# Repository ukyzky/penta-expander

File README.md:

# penta-expander

## ryo penta sequencer expander (eurorack 4HP)

Currently manufacturing no problem. It works fine.

## function

- per step **trigger** output
- per step on/off switch
- summed **trigger** output
- hold on/off switch
- hold input (signal high: hold on)

## notes

pcb v1 is main function.

pcb v1plus is sub function of gate to trigger converter x5.

If using pcb v1 only, it becomes per step gate output and summed gate output.
In summed gate output, it has a problem that a step produces 2 triggers because the step fall down signal overwraps the next step's clock.

If using pcb v1 and v1plus, it becomes per step trigger output and summed trigger output.
Above gate problem is resolved.

## bom

refer kicad files.

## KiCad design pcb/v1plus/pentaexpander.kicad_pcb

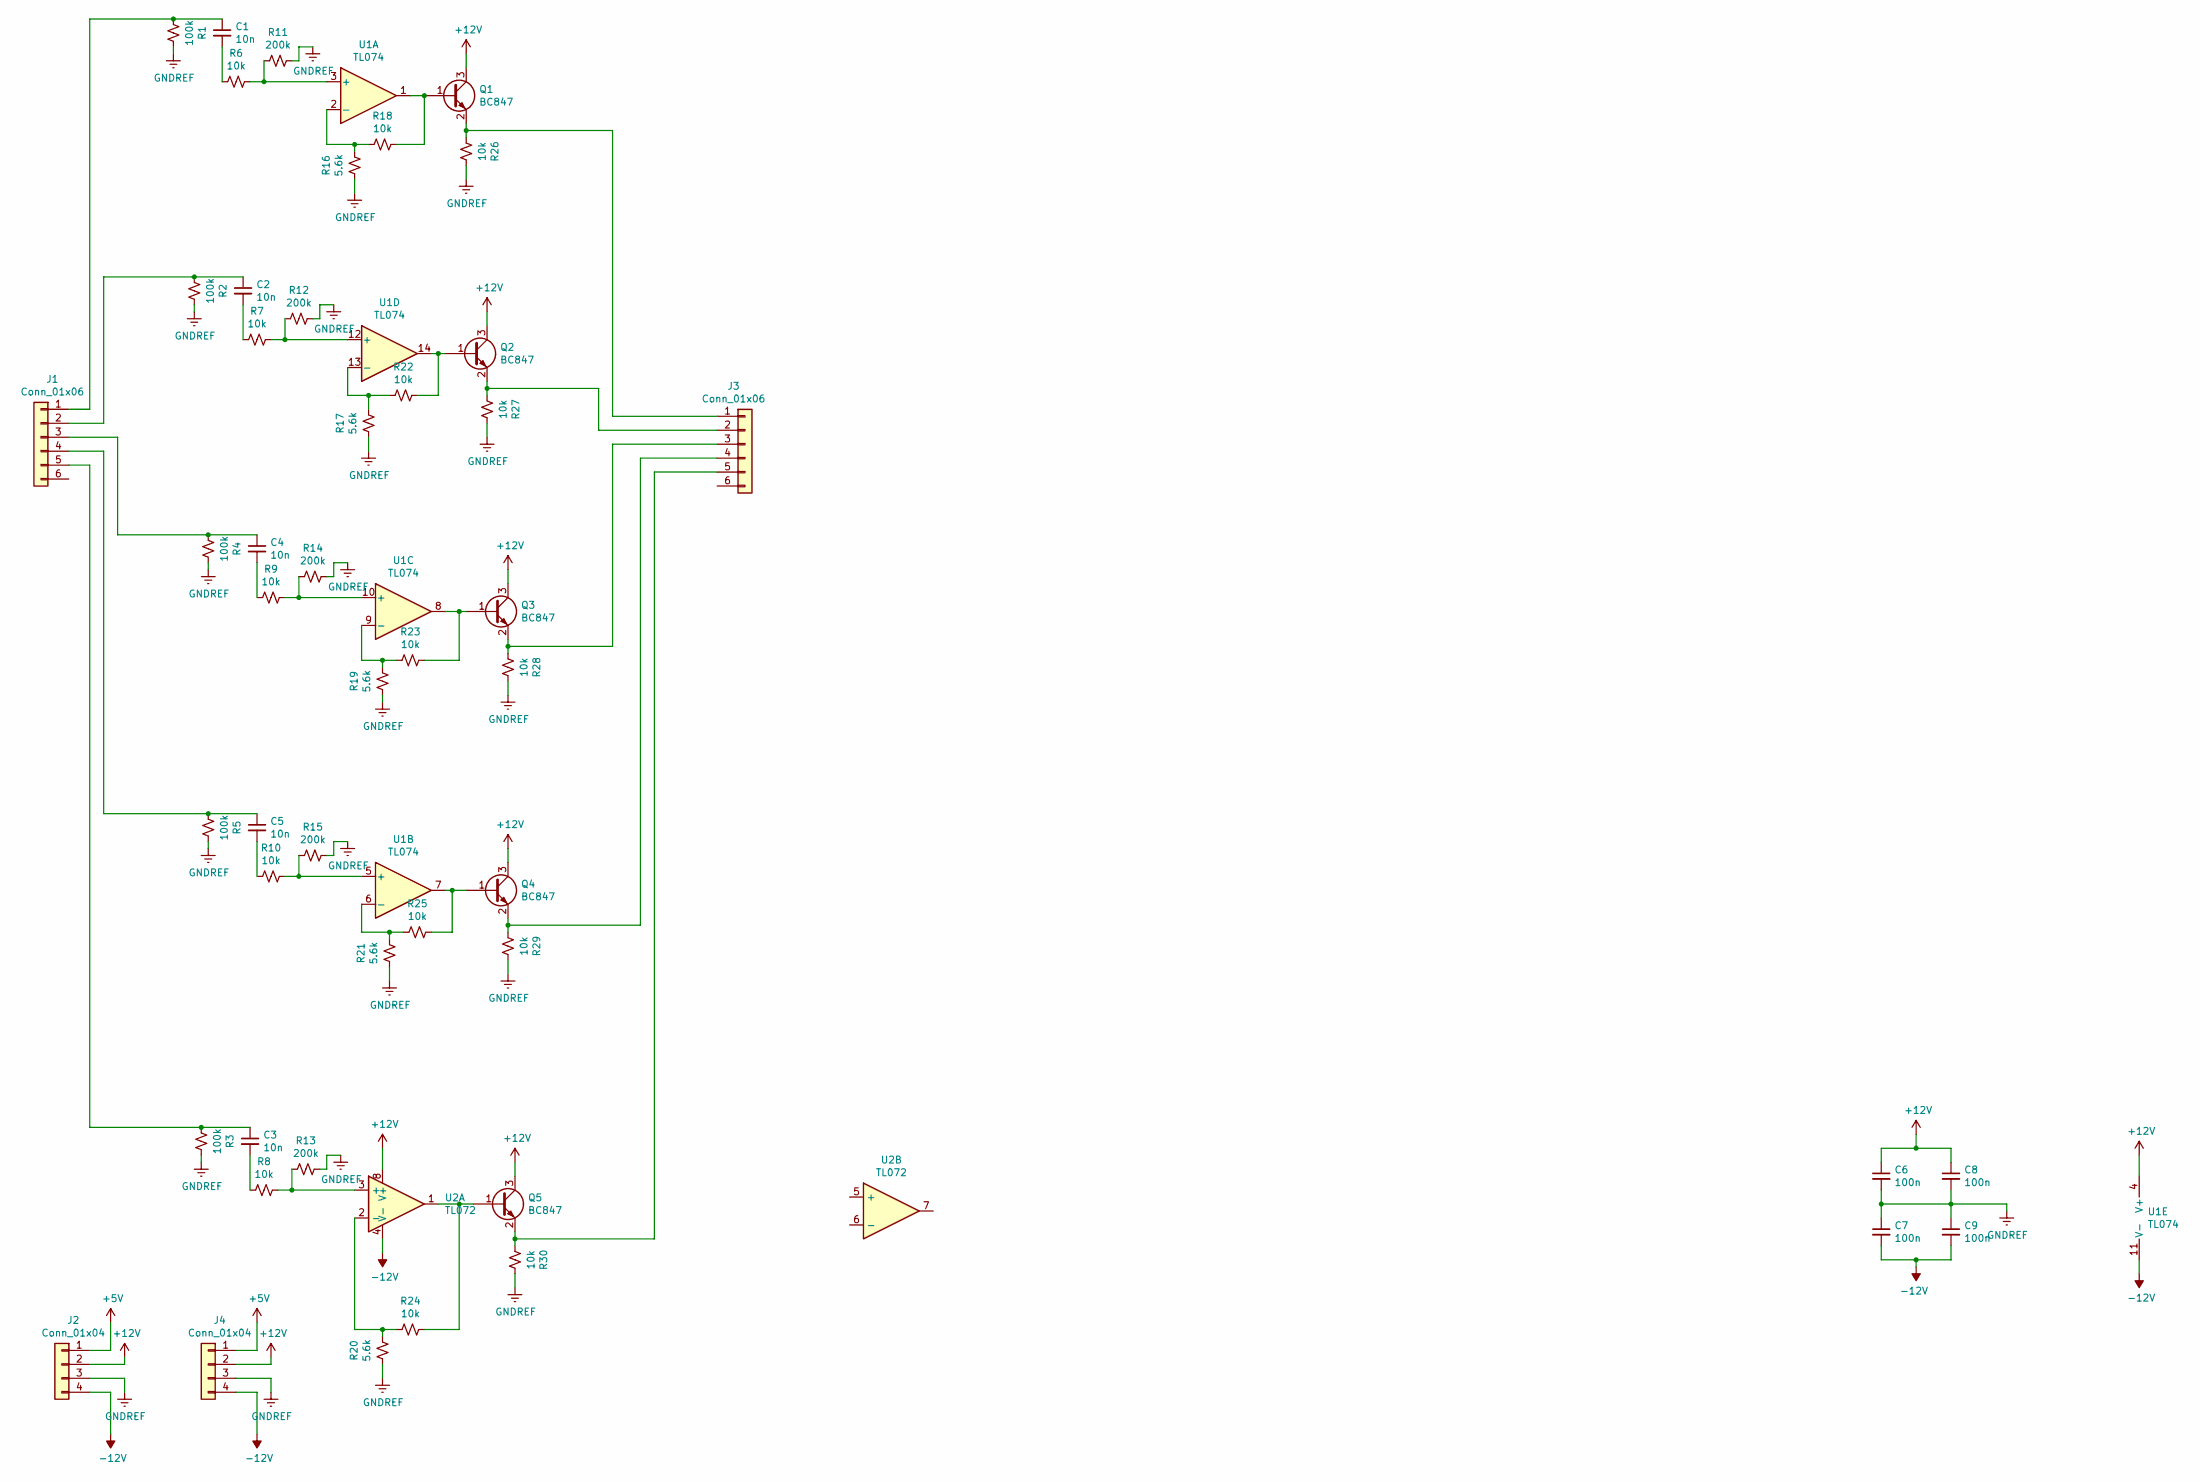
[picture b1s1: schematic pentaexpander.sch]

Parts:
C1, C2, C3, C4, C5: 10n; D_0805_2012Metric_Pad1.15x1.40mm_HandSolder
C6, C7, C8, C9: 100n; D_0805_2012Metric_Pad1.15x1.40mm_HandSolder
J1, J3: Conn_01x06; Pins_1x06_2.54mm_TH_SWD
J2, J4: Conn_01x04; Pins_1x04_2.54mm_TH
Q1, Q2, Q3, Q4, Q5: BC847; SOT-23
R1, R2, R3, R4, R5: 100k; R_0603_1608Metric_Pad1.05x0.95mm_HandSolder
R6, R7, R8, R9, R10, R18, R22, R23, R24, R25, R26, R27, R28, R29, R30: 10k; R_0603_1608Metric_Pad1.05x0.95mm_HandSolder
R11, R12, R13, R14, R15: 200k; R_0603_1608Metric_Pad1.05x0.95mm_HandSolder
R16, R17, R19, R20, R21: 5.6k; R_0603_1608Metric_Pad1.05x0.95mm_HandSolder
U1: TL074; SOIC-14_3.9x8.7mm_P1.27mm
U2: TL072; SOIC-8_3.9x4.9mm_Pitch1.27mm

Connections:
+5V: J2.1, J4.1
+12V: C6.1, C8.1, J2.2, J4.2, Q1.3 (C), Q2.3 (C), Q3.3 (C), Q4.3 (C), Q5.3 (C), U1.4 (V+), U2.8 (V+)
-12V: C7.2, C9.2, J2.4, J4.4, U1.11 (V-), U2.4 (V-)
GNDREF: C6.2, C7.1, C8.2, C9.1, J2.3, J4.3, R1.1, R2.1, R3.1, R4.1, R5.1, R11.1, R12.1, R13.1, R14.1, R15.1, R16.2, R17.2, R19.2, R20.2, R21.2, R26.1, R27.1, R28.1, R29.1, R30.1
unnamed: C1.1, J1.1, R1.2
unnamed: C1.2, R6.2
unnamed: C2.1, J1.2, R2.2
unnamed: C2.2, R7.2
unnamed: C3.1, J1.5, R3.2
unnamed: C3.2, R8.2
unnamed: C4.1, J1.3, R4.2
unnamed: C4.2, R9.2
unnamed: C5.1, J1.4, R5.2
unnamed: C5.2, R10.2
unnamed: J3.1, Q1.2 (E), R26.2
unnamed: J3.2, Q2.2 (E), R27.2
unnamed: J3.3, Q3.2 (E), R28.2
unnamed: J3.4, Q4.2 (E), R29.2
unnamed: J3.5, Q5.2 (E), R30.2
unnamed: Q1.1 (B), R18.1, U1.1
unnamed: Q2.1 (B), R22.1, U1.14
unnamed: Q3.1 (B), R23.1, U1.8
unnamed: Q4.1 (B), R25.1, U1.7
unnamed: Q5.1 (B), R24.1, U2.1
unnamed: R10.1, R15.2, U1.5 (+)
unnamed: R6.1, R11.2, U1.3 (+)
unnamed: R7.1, R12.2, U1.12 (+)
unnamed: R8.1, R13.2, U2.3 (+)
unnamed: R9.1, R14.2, U1.10 (+)
unnamed: R16.1, R18.2, U1.2 (-)
unnamed: R17.1, R22.2, U1.13 (-)
unnamed: R19.1, R23.2, U1.9 (-)
unnamed: R20.1, R24.2, U2.2 (-)
unnamed: R21.1, R25.2, U1.6 (-)

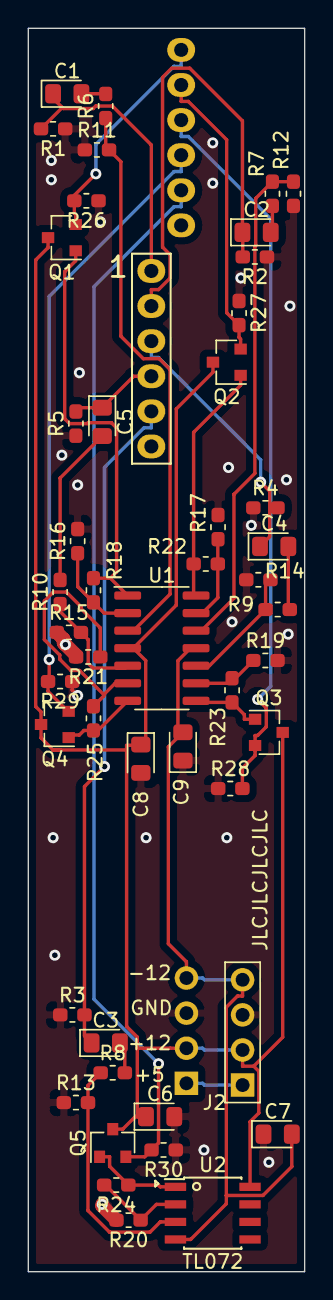
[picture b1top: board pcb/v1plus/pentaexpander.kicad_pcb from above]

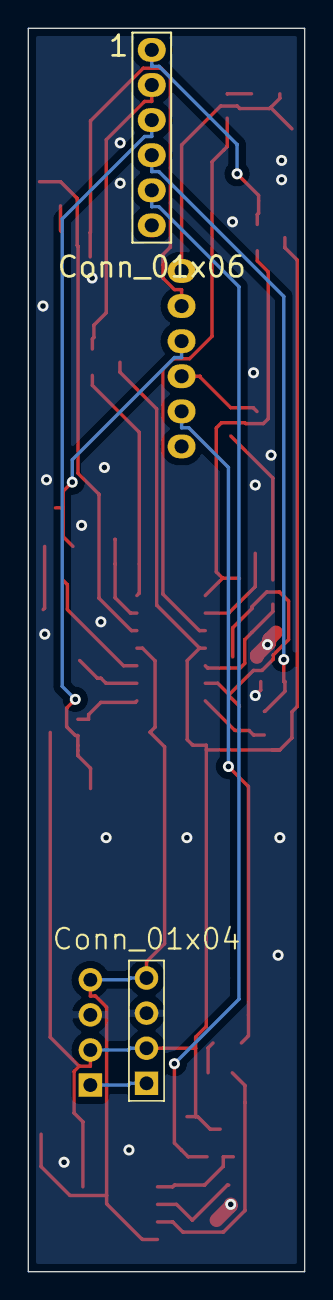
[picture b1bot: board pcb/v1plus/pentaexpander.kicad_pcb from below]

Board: 2 copper layers, 20.0 x 90.0 mm, 50 parts (2 on the bottom side), 34 nets.

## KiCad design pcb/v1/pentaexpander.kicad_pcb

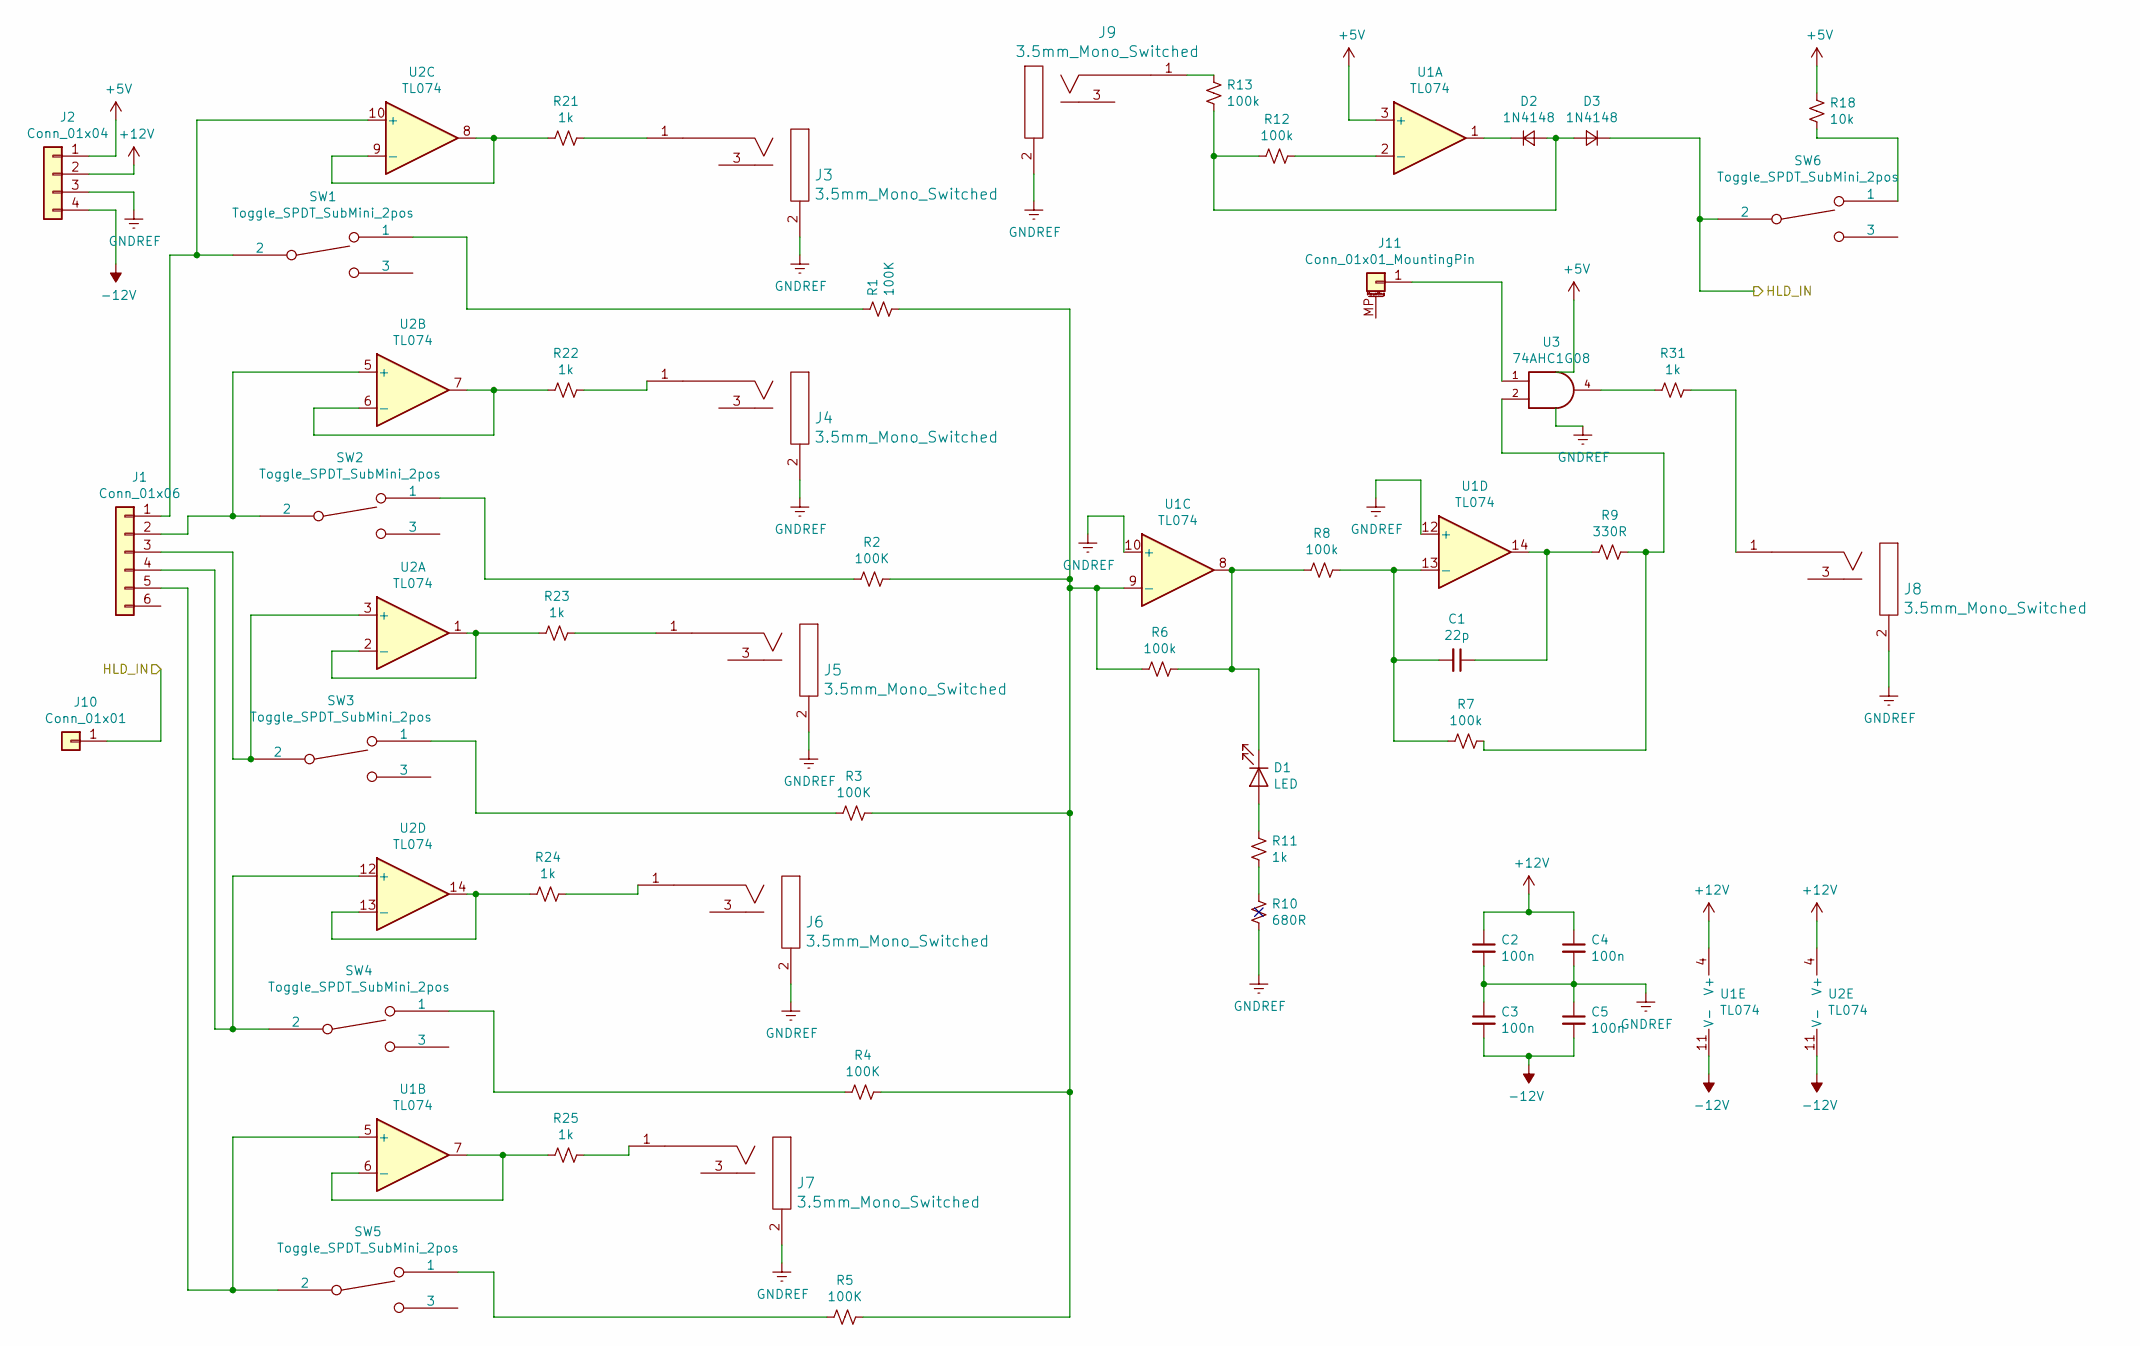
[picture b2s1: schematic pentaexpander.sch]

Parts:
C1: 22p; D_0805_2012Metric_Pad1.15x1.40mm_HandSolder
C2, C3, C4, C5: 100n; D_0805_2012Metric_Pad1.15x1.40mm_HandSolder
D1: LED; LED_D3.0mm
D2, D3: 1N4148; D_DO-15_P2.54mm_Vertical_AnodeUp
J1: Conn_01x06; Pins_1x06_2.54mm_TH_SWD
J2: Conn_01x04; Pins_1x04_2.54mm_TH
J3, J4, J5, J6, J7, J8, J9: 3.5mm_Mono_Switched; EighthInch_PJ398SM; Part Number WQP-WQP518MA
J10: Conn_01x01; PinHeader_1x01_P2.54mm_Vertical
J11: Conn_01x01_MountingPin; PinHeader_1x01_P2.54mm_Vertical
R1, R2, R3, R4, R5: 100K; R_0603_1608Metric_Pad1.05x0.95mm_HandSolder
R6, R7, R8, R12, R13: 100k; R_0603_1608Metric_Pad1.05x0.95mm_HandSolder
R9: 330R; R_0603_1608Metric_Pad1.05x0.95mm_HandSolder
R10: 680R; R_0603_1608Metric_Pad1.05x0.95mm_HandSolder
R11, R21, R22, R23, R24, R25, R31: 1k; R_0603_1608Metric_Pad1.05x0.95mm_HandSolder
R18: 10k; R_0603_1608Metric_Pad1.05x0.95mm_HandSolder
SW1, SW2, SW3, SW4, SW5, SW6: Toggle_SPDT_SubMini_2pos; Switch_Toggle_SPDT_SubMini; Part Number 200-MSP3-T2B3M2QE
U1, U2: TL074; SOIC-14_3.9x8.7mm_P1.27mm
U3: 74AHC1G08; SOT-23-5_HandSoldering

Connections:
+5V: J2.1, R18.1, U1.3 (+), U3.5 (VCC)
+12V: C2.1, C4.1, J2.2, U1.4 (V+), U2.4 (V+)
-12V: C3.2, C5.2, J2.4, U1.11 (V-), U2.11 (V-)
/HLD_IN: D3.1 (K), J10.1, SW6.2
GND: C2.2, C3.1, C4.2, C5.1, J2.3, J3.2 (SHEILD), J4.2 (SHEILD), J5.2 (SHEILD), J6.2 (SHEILD), J7.2 (SHEILD), J8.2 (SHEILD), J9.2 (SHEILD), R10.2, U1.10 (+), U1.12 (+), U3.3 (GND)
unnamed: C1.1, R9.2, U1.14
unnamed: C1.2, R7.2, R8.1, U1.13 (-)
unnamed: D1.1 (K), R6.1, R8.2, U1.8
unnamed: D1.2 (A), R11.1
unnamed: D2.1 (K), U1.1
unnamed: D2.2 (A), D3.2 (A), R12.2, R13.2
unnamed: J1.1, SW1.2, U2.10 (+)
unnamed: J1.2, SW2.2, U2.5 (+)
unnamed: J1.3, SW3.2, U2.3 (+)
unnamed: J1.4, SW4.2, U2.12 (+)
unnamed: J1.5, SW5.2, U1.5 (+)
unnamed: J3.1 (SIG), R21.1
unnamed: J4.1 (SIG), R22.1
unnamed: J5.1 (SIG), R23.1
unnamed: J6.1 (SIG), R24.1
unnamed: J7.1 (SIG), R25.1
unnamed: J8.1 (SIG), R31.1
unnamed: J9.1 (SIG), R13.1
unnamed 31: J11.1, U3.1; also elsewhere on the board
unnamed: R1.1, SW1.1
unnamed: R1.2, R2.1, R3.1, R4.1, R5.1, R6.2, U1.9 (-)
unnamed: R2.2, SW2.1
unnamed: R3.2, SW3.1
unnamed: R4.2, SW4.1
unnamed: R5.2, SW5.1
unnamed: R7.1, R9.1, U3.2
unnamed: R10.1, R11.2
unnamed: R12.1, U1.2 (-)
unnamed: R18.2, SW6.1
unnamed: R21.2, U2.8, U2.9 (-)
unnamed: R22.2, U2.6 (-), U2.7
unnamed: R23.2, U2.1, U2.2 (-)
unnamed: R24.2, U2.13 (-), U2.14
unnamed: R25.2, U1.6 (-), U1.7
unnamed: R31.2, U3.4

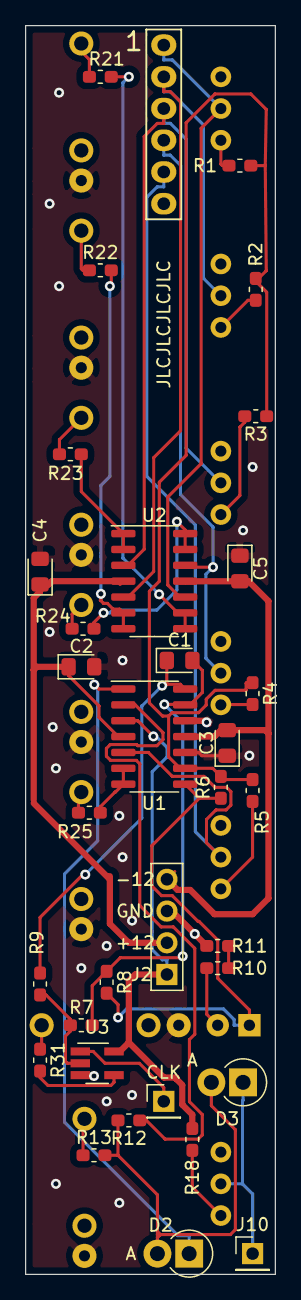
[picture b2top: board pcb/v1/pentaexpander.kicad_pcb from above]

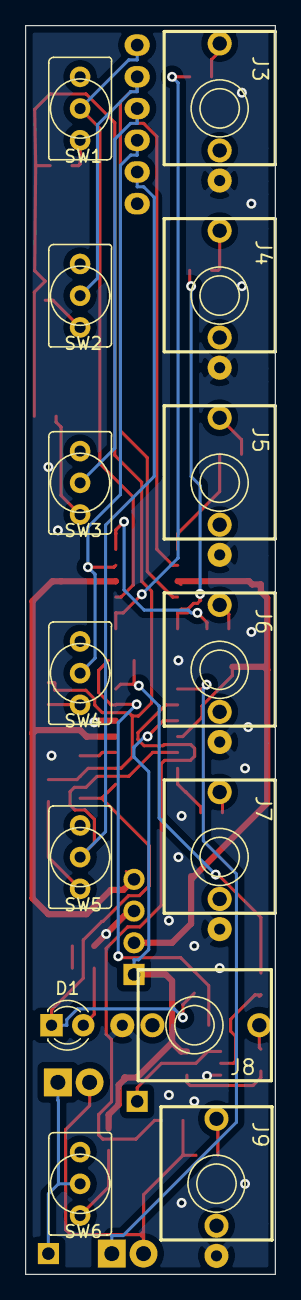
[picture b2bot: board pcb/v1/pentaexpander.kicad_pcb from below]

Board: 2 copper layers, 20.0 x 100.0 mm, 48 parts (14 on the bottom side), 40 nets.

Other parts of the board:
CLK: Conn_01x01_MountingPin; PinHeader_1x01_P2.54mm_Vertical

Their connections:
unnamed 31: CLK.1; also elsewhere on the board

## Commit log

2021-05-31 Update gitignore.
2021-05-31 Add pcb and panel v1.
2021-07-22 Add pcb v1plus.
2021-08-22 Add images.
